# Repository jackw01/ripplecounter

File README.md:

# ripplecounter

## What?

* Control the position and speed of a brushed DC motor, *any* brushed DC motor
* No sensors, electromechanical components, or extra wiring needed
* Measure motor current with no extra complexity or cost
* Lower resolution than an encoder, but good enough for many applications
* Use almost any microcontroller, not just a Raspberry Pi Pico

### How Does It Work?

DC motors work internally by using a commutator and brushes, essentially a rotary switch that applies power to each of the motor’s coils in sequence as it rotates. By sensing, amplifying, and filtering the current flowing through the motor, the current ripples that occur as the motor rotates and each coil is energized can be counted by a microcontroller.

### How Well Does It Work?

If component values for the signal conditioning circuit are selected properly, surprisingly well.

## Circuit Design

[Schematic as PDF](pcb/schematic%20rev1%2020230427-01.pdf)

The signal conditioning circuit is based on the designs described in [Texas Instruments application note TIDA-01421](https://www.ti.com/lit/ug/tidud30a/tidud30a.pdf?ts=1682413672035) and [Microchip application note AN3049](http://ww1.microchip.com/downloads/en/Appnotes/Sensorless-Position-Control-of-Brushed-DC-Motor-Using-Ripple-Counting-Technique-00003049A.pdf). The initial current sense amplifier is implemented using the [Texas Instruments INA181 IC](https://www.mouser.com/datasheet/2/405/ina181-1109801.pdf) (U202) with a current sense resistor directly in series with the motor, allowing for bidirectional current sensing. The remaining amplifier and filtering stages are implemented using an LM324 (U203) general-purpose quad op amp. U203B is used as an active bandpass filter, which works with two other RC low-pass filters to eliminate high frequency noise and low-frequency oscillations in current caused by varying load on the motor. U203C is used to subtract large and relatively slow changes in the signal, such as the motor's inrush current spike. U203D is used as a comparator with hysteresis to generate a clean output signal.

Purple: filtered, amplified motor current waveform (TP211); Yellow: output signal (TP215)

### Design Modification Guide

The component values used in this circuit will need to be adjusted for optimal performance with any motor - as-is, the values in the schematic were chosen for N20-size gearmotors and will work decently well for similar small motors.

When modifying the design for a different motor:

* The current sense resistor (R201/R202) value and power rating **must** be selected to keep the power dissipation in the resistor well within its specified power rating. For larger motors with high inrush/stall current, the pulse load capability of the resistor should also be considered.
* The current sense resistor value and the gain of the current sense amplifier (the INA181 IC used comes in four different fixed-gain options) **must** be selected to prevent clipping at the  output of the current sense amplifier with maximum motor current: `I_motor_max * R_isense * Gain < (3.3V / 2)`.

Several other components should be considered after choosing the sense resistor and amplifier:

* The gain of the active bandpass filter, set by R213 and R214, should be selected experimentally to minimize clipping at the output of the filter (TP211).
* The gain of the differential amplifier, set by R216-R219, should be selected experimentally to provide a clean output from the comparator (TP215). C214 should be changed if R217/R218 are changed by more than an order of magnitude.
* The cutoff frequencies of the active bandpass filter and the RC low-pass filter formed by R215 and C213 may need to be changed depending on the speed of the motor used. It is recommended that the cutoff frequency of R215/C213 be at least the motor's ripple frequency at full speed and the cutoff frequency of R214/C210 be at least two times that frequency.

## Development Board

The ripplecounter development board incorporates a Raspberry Pi Pico microcontroller, two motor drivers, and two copies of the signal conditioning circuit. The board is designed to allow the use of Texas Instruments DRV8231, DRV8231A, DRV8251, or DRV8251A SO-8 package H-bridge motor driver ICs, for up to 50V motor supply voltage and 4.1A peak output current. An external motor driver may also be used. The development board is designed to be manufactured by any low-cost PCB supplier, such as JLCPCB or PCBWay, and easily assembled and modified by hand - the smallest passive components used are 0603 size.

The top PCB is minimally assembled for manually testing the signal conditioning circuit; the bottom PCB has been modified to control a camera slider for focus stacking macrophotography.

### License
The schematic is in the public domain - you are free to use this circuit design for any purpose, without attribution. The PCB layout and Gerber files for the development board  are released under the CERN Open Hardware Licence Version 2 - Weakly Reciprocal (CERN-OHL-W V2).

## Firmware

Basic firmware using the Raspberry Pi Pico C SDK is provided, which moves the motor while printing the position, speed, and current draw via UART. All important constants are documented in `ripplecounter_motor.c`.

Note: When used with the DRV8x21 motor controller on the development board, this firmware brakes the motor (as opposed to letting it coast) when it is not running, which is desirable for applications that require position control. If the motor is forcibly rotated while it is not running, the change in position will be detected via the ripple counter circuit, but sensing the *direction* of rotation is not implemented. If this functionality is needed, it can be implemented by sampling the motor current value read through the ADC, which will be negative or positive depending on which direction the motor is being turned.

### License

All code provided is released under the MIT License.

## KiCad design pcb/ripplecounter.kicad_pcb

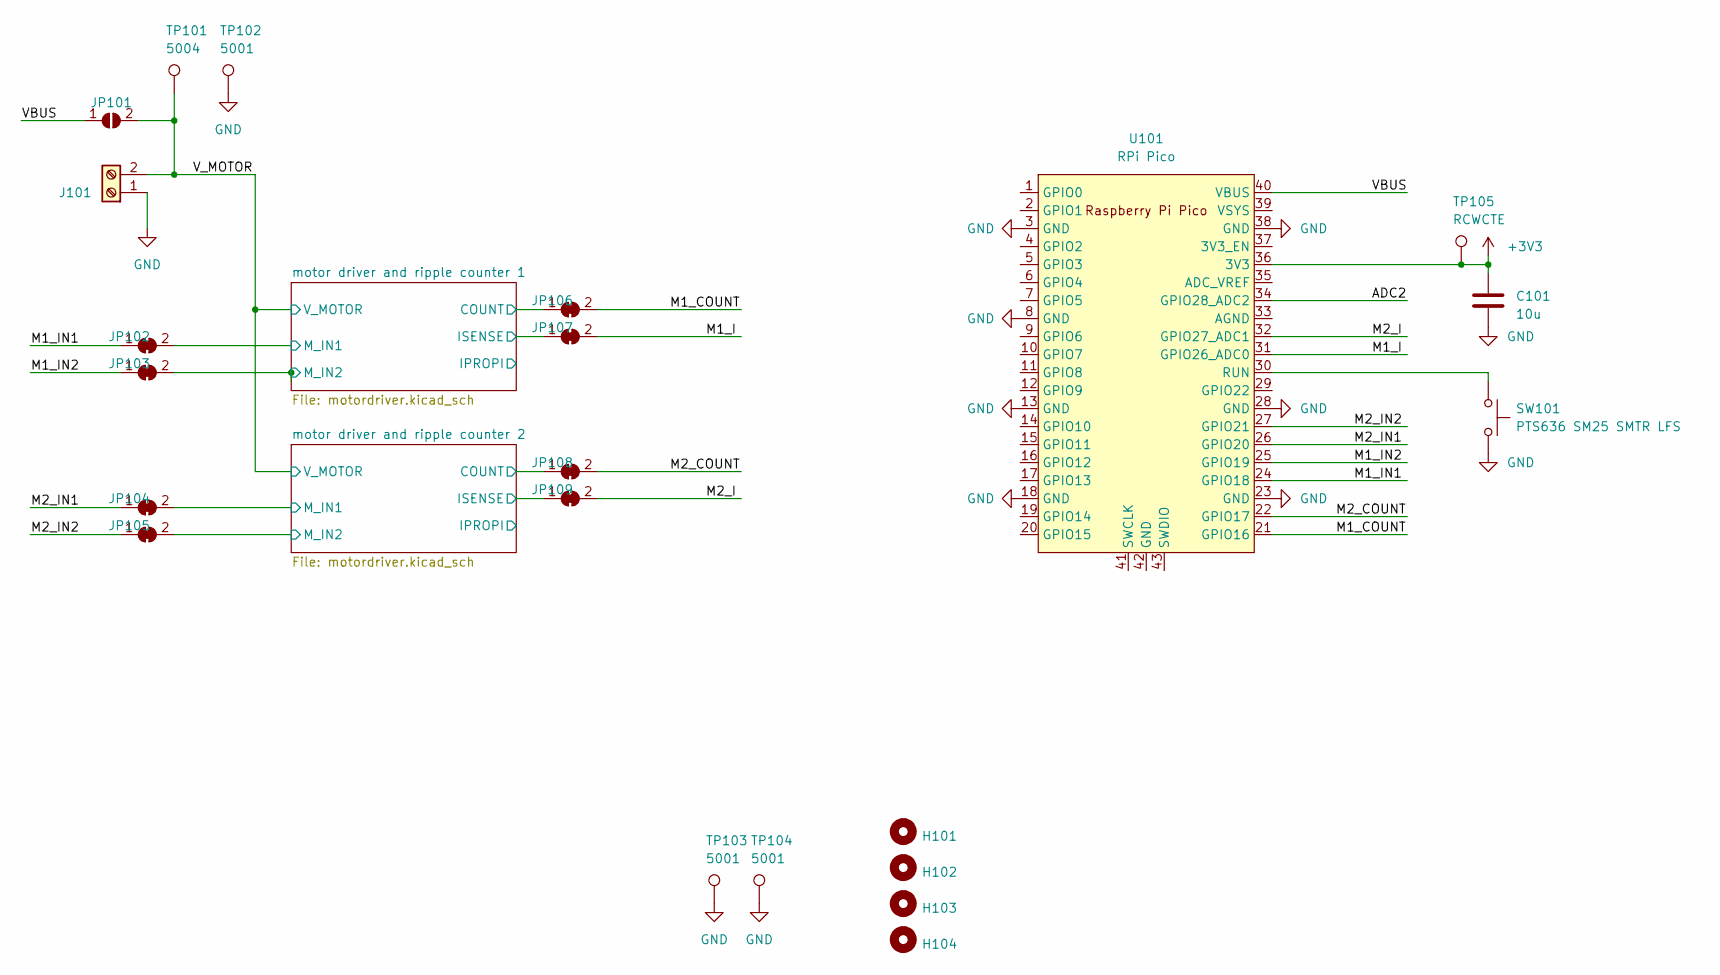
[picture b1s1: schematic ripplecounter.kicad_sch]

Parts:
C101: 10u; C_1206_3216Metric
H101, H102, H103, H104: MountingHole_2.2mm_M2_ISO14580
J101: TerminalBlock_4Ucon_1x02_P3.50mm_Horizontal
JP101: Jumper_0603
JP102, JP103, JP106, JP107, JP108, JP109: Jumper_0603_Bridged
JP104, JP105: 0603_Closed; Jumper_0603_Bridged
SW101: PTS636 SM25 SMTR LFS; SW_SPST_CK_RS282G05A3
TP101: 5004; TestPoint_Keystone_5000-5004_Miniature
TP102, TP103, TP104: 5001; TestPoint_Keystone_5000-5004_Miniature
TP105: RCWCTE; TestPoint_Keystone_5015_Micro-Minature
U101: RPi Pico; RPi_Pico_SMD_TH

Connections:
+3V3: C101.1, TP105.1, U101.36 (3V3); also elsewhere on the board
/ADC2: U101.34 (GPIO28_ADC2)
/M1_COUNT: JP106.2 (B), U101.21 (GPIO16)
/M1_I: JP107.2 (B), U101.31 (GPIO26_ADC0)
/M1_IN1: JP102.1 (A), U101.24 (GPIO18)
/M1_IN2: JP103.1 (A), U101.25 (GPIO19)
/M2_COUNT: JP108.2 (B), U101.22 (GPIO17)
/M2_I: JP109.2 (B), U101.32 (GPIO27_ADC1)
/M2_IN1: JP104.1 (A), U101.26 (GPIO20)
/M2_IN2: JP105.1 (A), U101.27 (GPIO21)
/VBUS: JP101.1 (A), U101.40 (VBUS)
/V_MOTOR: J101.2, JP101.2 (B), TP101.1; also elsewhere on the board
/motor driver and ripple counter 1/COUNT: JP106.1 (A); also elsewhere on the board
/motor driver and ripple counter 1/ISENSE: JP107.1 (A); also elsewhere on the board
/motor driver and ripple counter 1/M_IN1: JP102.2 (B); also elsewhere on the board
/motor driver and ripple counter 1/M_IN2: JP103.2 (B); also elsewhere on the board
/motor driver and ripple counter 2/COUNT: JP108.1 (A); also elsewhere on the board
/motor driver and ripple counter 2/ISENSE: JP109.1 (A); also elsewhere on the board
/motor driver and ripple counter 2/M_IN1: JP104.2 (B); also elsewhere on the board
/motor driver and ripple counter 2/M_IN2: JP105.2 (B); also elsewhere on the board
GND: C101.2, J101.1, SW101.2, TP102.1, TP103.1, TP104.1, U101.3 (GND), U101.8 (GND), U101.13 (GND), U101.18 (GND), U101.23 (GND), U101.28 (GND), U101.38 (GND); also elsewhere on the board
unnamed: SW101.1, U101.30 (RUN)

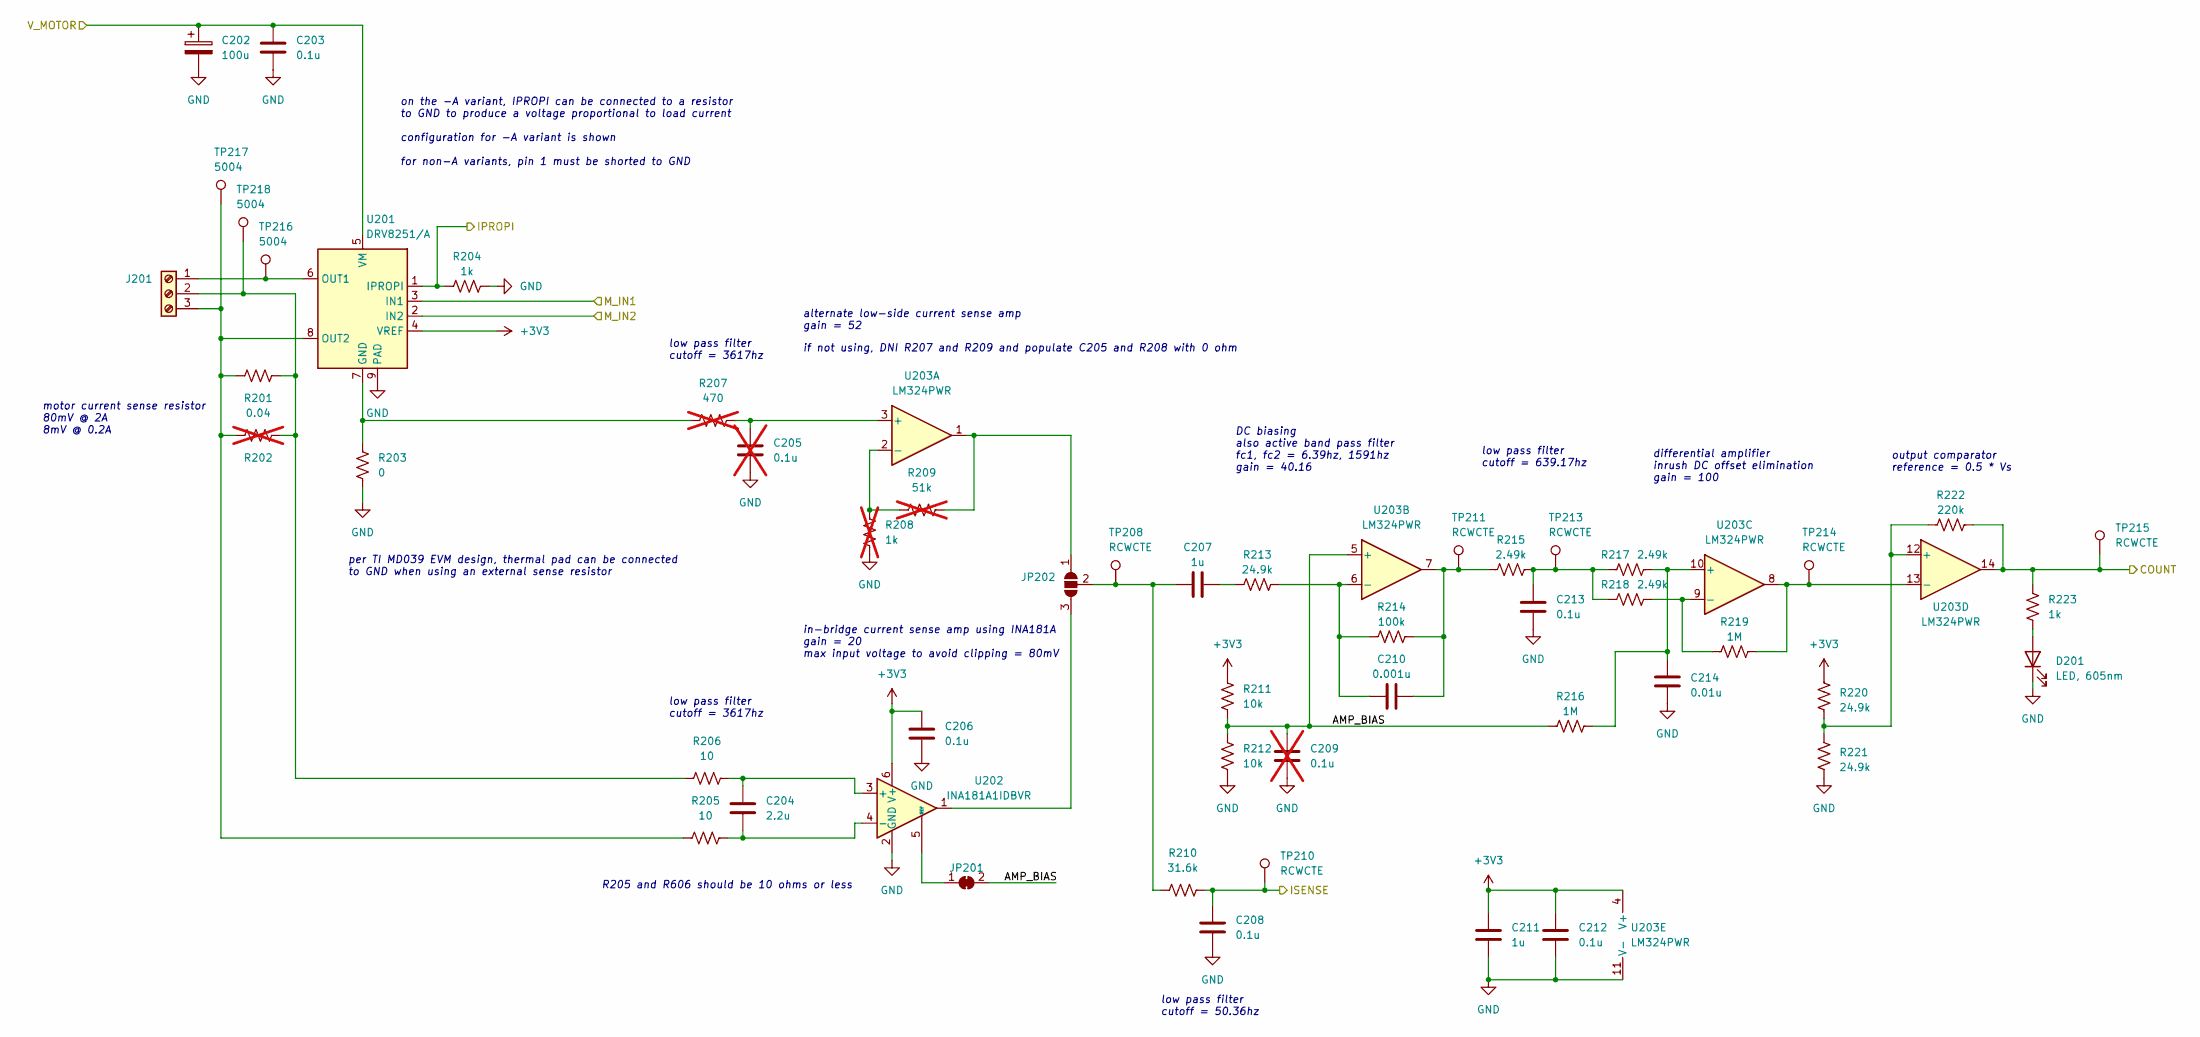
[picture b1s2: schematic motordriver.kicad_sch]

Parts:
C202: 100u; CP_Radial_D8.0mm_P3.50mm
C203, C206, C208, C212, C213: 0.1u; C_0603_1608Metric
C204: 2.2u; C_0603_1608Metric
C205, C209: 0.1u; C_0603_1608Metric; not fitted
C207, C211: 1u; C_0603_1608Metric
C210: 0.001u; C_0603_1608Metric
C214: 0.01u; C_0603_1608Metric
D201: LED, 605nm; LED_0603_1608Metric
J201: TerminalBlock_4Ucon_1x03_P3.50mm_Horizontal
JP201: Jumper_0603_Bridged
JP202: Bi_0603_Open
R201: 0.04; R_1206_3216Metric
R202: R_2512_6332Metric; not fitted
R203: 0; R_1206_3216Metric
R204, R223: 1k; R_0603_1608Metric
R205, R206: 10; R_0603_1608Metric
R207: 470; R_0603_1608Metric; not fitted
R208: 1k; R_0603_1608Metric; not fitted
R209: 51k; R_0603_1608Metric; not fitted
R210: 31.6k; R_0603_1608Metric
R211, R212: 10k; R_0603_1608Metric
R213, R220, R221: 24.9k; R_0603_1608Metric
R214: 100k; R_0603_1608Metric
R215, R217, R218: 2.49k; R_0603_1608Metric
R216, R219: 1M; R_0603_1608Metric
R222: 220k; R_0603_1608Metric
TP208, TP210, TP211, TP213, TP214, TP215: RCWCTE; TestPoint_Keystone_5015_Micro-Minature
TP216, TP217, TP218: 5004; TestPoint_Keystone_5000-5004_Miniature
U201: DRV8251/A; HSOP-8-1EP_3.9x4.9mm_P1.27mm_EP2.41x3.1mm_ThermalVias_HandS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
U202: INA181A1IDBVR; SOT-23-6
U203: LM324PWR; TSSOP-14_4.4x5mm_P0.65mm

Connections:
+3V3: C206.1, C211.1, C212.1, R211.1, R220.1, U201.4 (VREF), U202.6 (V+), U203.4 (V+); also elsewhere on the board
/V_MOTOR: C202.1, C203.1, U201.5 (VM); also elsewhere on the board
/motor driver and ripple counter 1/AMP_BIAS: C209.2, JP201.2 (B), R211.2, R212.1, R216.2, U203.5 (+)
/motor driver and ripple counter 1/COUNT: R222.1, R223.1, TP215.1, U203.14; also elsewhere on the board
/motor driver and ripple counter 1/IPROPI: R204.1, U201.1 (IPROPI)
/motor driver and ripple counter 1/ISENSE: C208.2, R210.2, TP210.1; also elsewhere on the board
/motor driver and ripple counter 1/M_IN1: U201.3 (IN1); also elsewhere on the board
/motor driver and ripple counter 1/M_IN2: U201.2 (IN2); also elsewhere on the board
GND: C202.2, C203.2, C205.2, C206.2, C208.1, C209.1, C211.2, C212.2, C213.1, C214.1, D201.1 (K), R203.1, R204.2, R208.2, R212.2, R221.2, U201.9 (PAD), U202.2 (GND), U203.11 (V-); also elsewhere on the board
unnamed: C207.2, R213.1
unnamed: C210.2, R214.1, R215.1, TP211.1, U203.7
unnamed: C213.2, R215.2, R217.1, R218.1, TP213.1
unnamed: D201.2 (A), R223.2
unnamed: J201.1, TP216.1, U201.6 (OUT1)
unnamed: J201.2, R201.2, R202.2, R206.2, TP218.1
unnamed: J201.3, R201.1, R202.1, R205.2, TP217.1, U201.8 (OUT2)
unnamed: JP201.1 (A), U202.5 (REF)
unnamed: JP202.1 (A), R209.1, U203.1
unnamed: JP202.3 (B), U202.1
unnamed: C207.1, JP202.2 (C), R210.1, TP208.1
unnamed: R203.2, R207.2, U201.7 (GND)
unnamed: C204.1, R206.1, U202.3 (+)
unnamed: C204.2, R205.1, U202.4 (-)
unnamed: C205.1, R207.1, U203.3 (+)
unnamed: R208.1, R209.2, U203.2 (-)
unnamed: C210.1, R213.2, R214.2, U203.6 (-)
unnamed: C214.2, R216.1, R217.2, U203.10 (+)
unnamed: R218.2, R219.2, U203.9 (-)
unnamed: R220.2, R221.1, R222.2, U203.12 (+)
unnamed: R219.1, TP214.1, U203.8, U203.13 (-)

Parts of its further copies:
C302: 100u; CP_Radial_D8.0mm_P3.50mm
C303, C306, C308, C312, C313: 0.1u; C_0603_1608Metric
C304: 2.2u; C_0603_1608Metric
C305, C309: 0.1u; C_0603_1608Metric; not fitted
C307, C311: 1u; C_0603_1608Metric
C310: 0.001u; C_0603_1608Metric
C314: 0.01u; C_0603_1608Metric
D301: LED, 605nm; LED_0603_1608Metric
J301: TerminalBlock_4Ucon_1x03_P3.50mm_Horizontal
JP301: Jumper_0603_Bridged
JP302: Bi_0603_Open
R301: 0.04; R_1206_3216Metric
R302: R_2512_6332Metric; not fitted
R303: 0; R_1206_3216Metric
R304, R323: 1k; R_0603_1608Metric
R305, R306: 10; R_0603_1608Metric
R307: 470; R_0603_1608Metric; not fitted
R308: 1k; R_0603_1608Metric; not fitted
R309: 51k; R_0603_1608Metric; not fitted
R310: 31.6k; R_0603_1608Metric
R311, R312: 10k; R_0603_1608Metric
R313, R320, R321: 24.9k; R_0603_1608Metric
R314: 100k; R_0603_1608Metric
R315, R317, R318: 2.49k; R_0603_1608Metric
R316, R319: 1M; R_0603_1608Metric
R322: 220k; R_0603_1608Metric
TP308, TP310, TP311, TP313, TP314, TP315: RCWCTE; TestPoint_Keystone_5015_Micro-Minature
TP316, TP317, TP318: 5004; TestPoint_Keystone_5000-5004_Miniature
U301: DRV8251/A; HSOP-8-1EP_3.9x4.9mm_P1.27mm_EP2.41x3.1mm_ThermalVias_HandS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
U302: INA181A1IDBVR; SOT-23-6
U303: LM324PWR; TSSOP-14_4.4x5mm_P0.65mm

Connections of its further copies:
+3V3: C306.1, C311.1, C312.1, R311.1, R320.1, U301.4 (VREF), U302.6 (V+), U303.4 (V+); also elsewhere on the board
/V_MOTOR: C302.1, C303.1, U301.5 (VM); also elsewhere on the board
/motor driver and ripple counter 2/AMP_BIAS: C309.2, JP301.2 (B), R311.2, R312.1, R316.2, U303.5 (+)
/motor driver and ripple counter 2/COUNT: R322.1, R323.1, TP315.1, U303.14; also elsewhere on the board
/motor driver and ripple counter 2/IPROPI: R304.1, U301.1 (IPROPI)
/motor driver and ripple counter 2/ISENSE: C308.2, R310.2, TP310.1; also elsewhere on the board
/motor driver and ripple counter 2/M_IN1: U301.3 (IN1); also elsewhere on the board
/motor driver and ripple counter 2/M_IN2: U301.2 (IN2); also elsewhere on the board
GND: C302.2, C303.2, C305.2, C306.2, C308.1, C309.1, C311.2, C312.2, C313.1, C314.1, D301.1 (K), R303.1, R304.2, R308.2, R312.2, R321.2, U301.9 (PAD), U302.2 (GND), U303.11 (V-); also elsewhere on the board
unnamed: C307.2, R313.1
unnamed: C310.2, R314.1, R315.1, TP311.1, U303.7
unnamed: C313.2, R315.2, R317.1, R318.1, TP313.1
unnamed: D301.2 (A), R323.2
unnamed: J301.1, TP316.1, U301.6 (OUT1)
unnamed: J301.2, R301.2, R302.2, R306.2, TP318.1
unnamed: J301.3, R301.1, R302.1, R305.2, TP317.1, U301.8 (OUT2)
unnamed: JP301.1 (A), U302.5 (REF)
unnamed: JP302.1 (A), R309.1, U303.1
unnamed: JP302.3 (B), U302.1
unnamed: C307.1, JP302.2 (C), R310.1, TP308.1
unnamed: R303.2, R307.2, U301.7 (GND)
unnamed: C304.1, R306.1, U302.3 (+)
unnamed: C304.2, R305.1, U302.4 (-)
unnamed: C305.1, R307.1, U303.3 (+)
unnamed: R308.1, R309.2, U303.2 (-)
unnamed: C310.1, R313.2, R314.2, U303.6 (-)
unnamed: C314.2, R316.1, R317.2, U303.10 (+)
unnamed: R318.2, R319.2, U303.9 (-)
unnamed: R320.2, R321.1, R322.2, U303.12 (+)
unnamed: R319.1, TP314.1, U303.8, U303.13 (-)

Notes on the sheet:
low pass filter cutoff = 50.36hz
low pass filter cutoff = 3617hz
DC biasing also active band pass filter fc1, fc2 = 6.39hz, 1591hz gain = 40.16
low pass filter cutoff = 3617hz
if not using, DNI R207 and R209 and populate C205 and R208 with 0 ohm
alternate low-side current sense amp gain = 52
low pass filter cutoff = 639.17hz
motor current sense resistor 80mV @ 2A 8mV @ 0.2A
per TI MD039 EVM design, thermal pad can be connected to GND when using an external sense resistor
in-bridge current sense amp using INA181A gain = 20 max input voltage to avoid clipping = 80mV
differential amplifier inrush DC offset elimination gain = 100
R205 and R606 should be 10 ohms or less
output comparator reference = 0.5 * Vs
on the -A variant, IPROPI can be connected to a resistor to GND to produce a voltage proportional to load current configuration for -A variant is shown for non-A variants, pin 1 must be shorted to GND

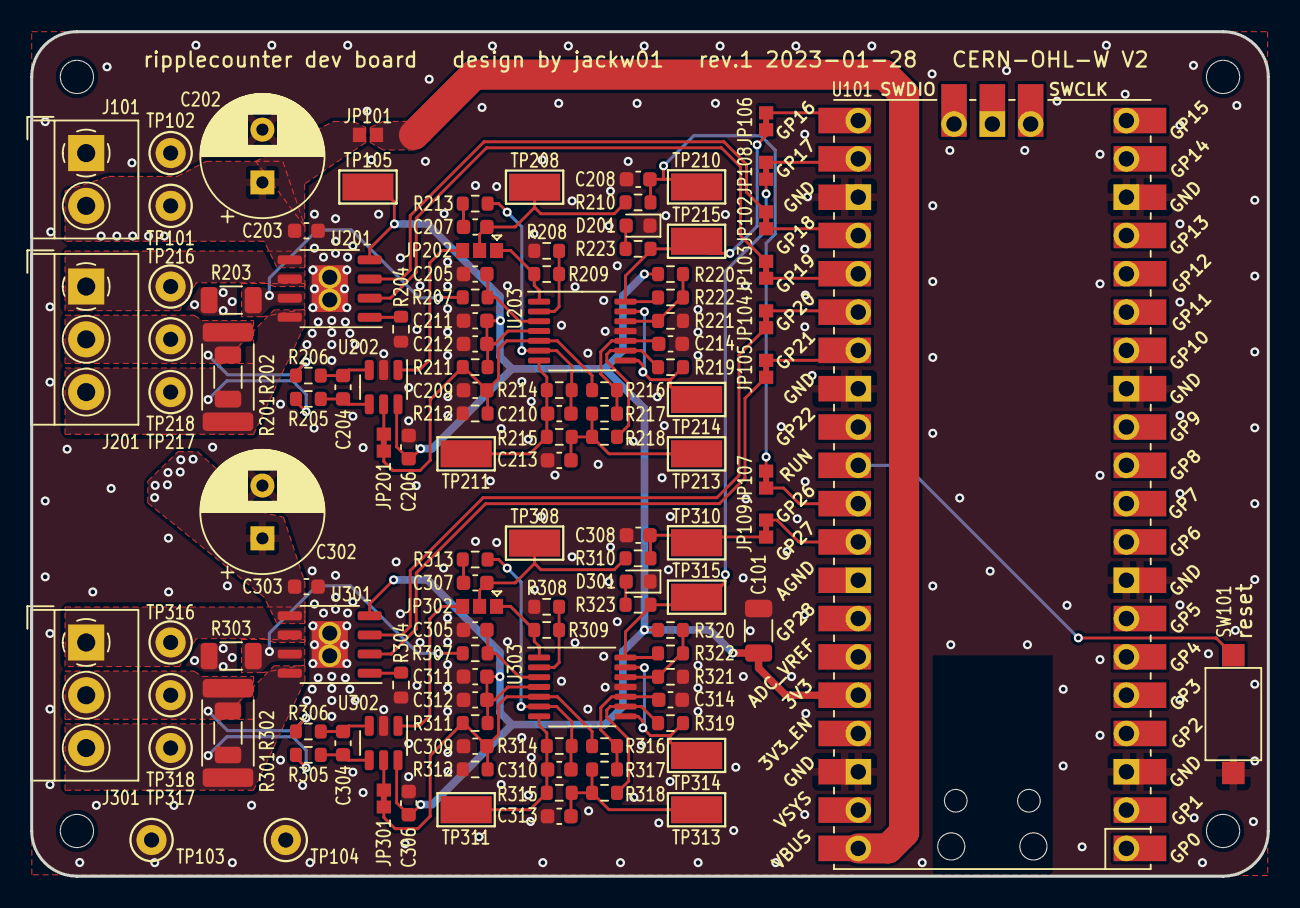
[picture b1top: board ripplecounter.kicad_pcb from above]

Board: 2 copper layers, 82.0 x 56.0 mm, 126 parts (0 on the bottom side), 67 nets.

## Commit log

2023-04-25 add pcb
2023-04-25 add license
2023-04-27 demo firmware (need to test again)
2023-04-27 readme
2023-04-28 readme and schematic
2023-05-02 fix demo firmware
2023-05-02 readme and photos

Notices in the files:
pcb/ripplecounter.kicad_pcb:
ripplecounter dev board design by jackw01 rev.1 2023-01-28 CERN-OHL-W V2
Released under the CERN-OHL-W V2 license
